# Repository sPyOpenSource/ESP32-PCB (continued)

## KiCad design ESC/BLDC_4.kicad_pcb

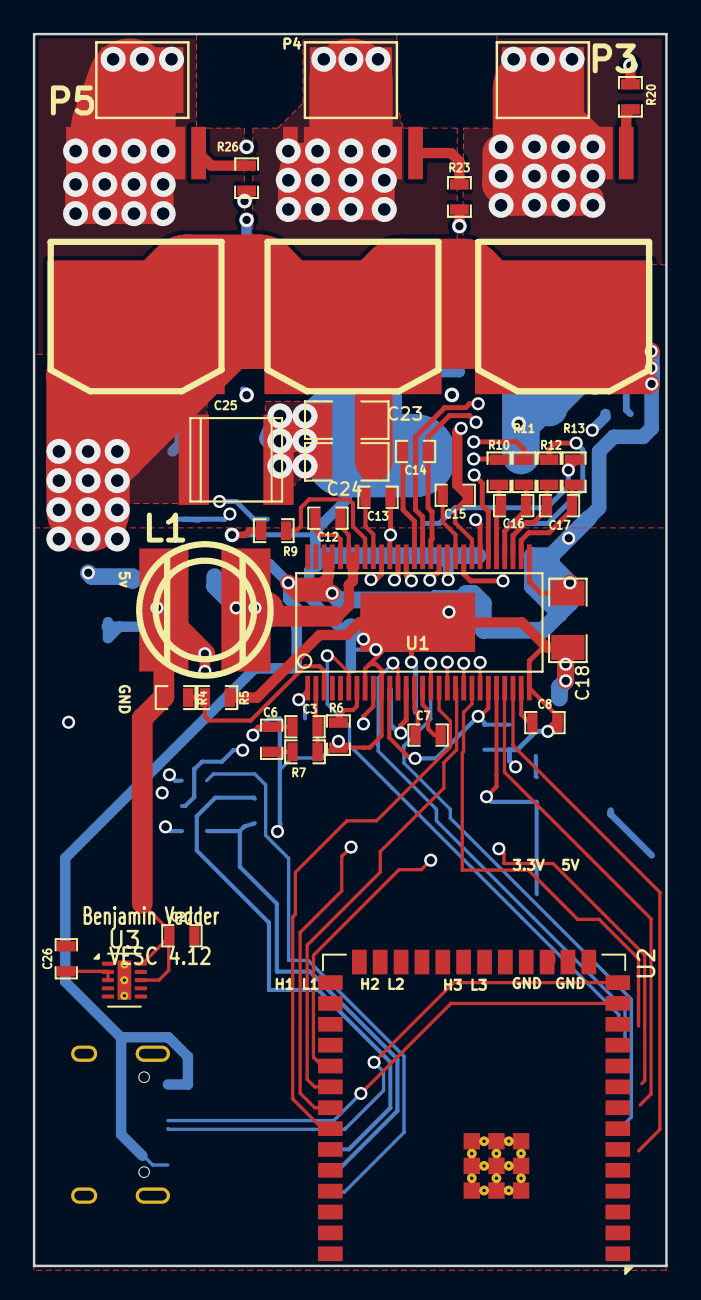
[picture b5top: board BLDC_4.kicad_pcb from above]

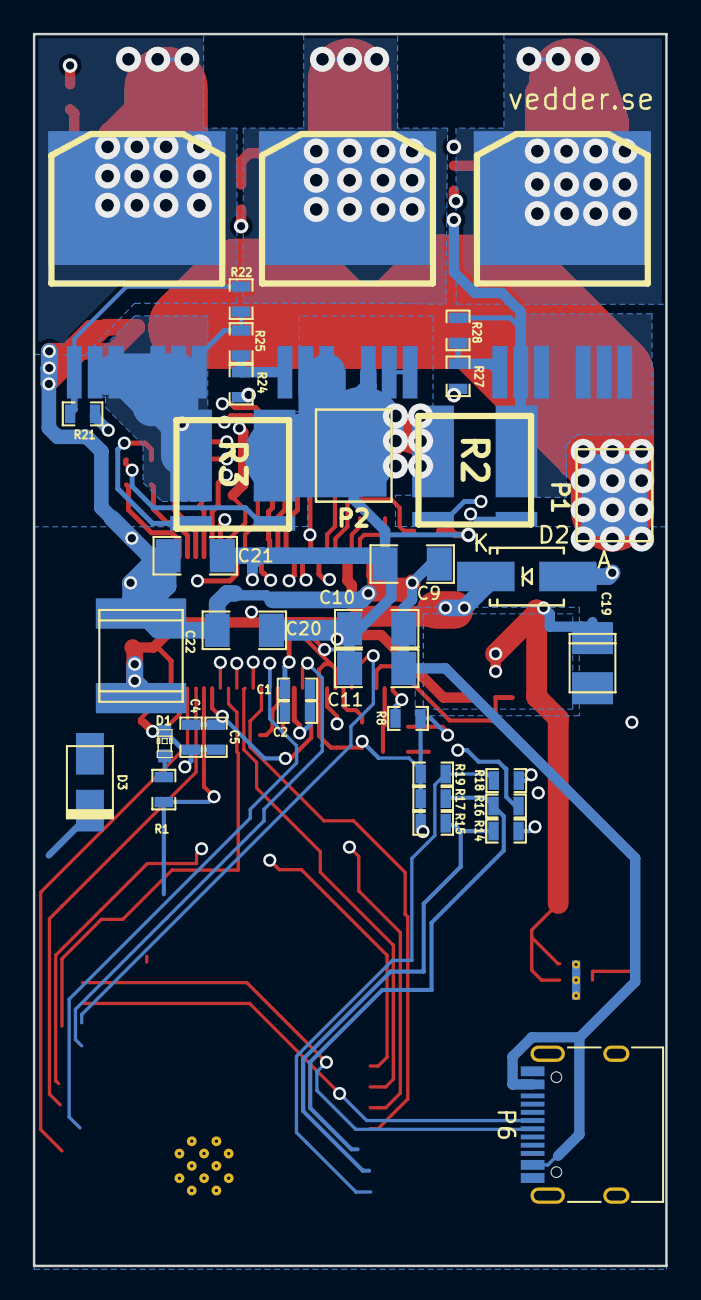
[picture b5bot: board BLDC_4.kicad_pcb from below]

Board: 4 copper layers, 38.5 x 75.0 mm, 74 parts (36 on the bottom side), 58 nets.

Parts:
C1, C2, C4, C5, C8: 2.2u; SMD-0603_c
C3: 120p; SMD-0603_c
C6: 6.8n; SMD-0603_c
C7: 22n; SMD-0603_c
C9, C10, C11, C18, C20, C21, C23, C24: 10u,50V; SMD-1206
C12: 100n; SMD-0603_c
C13, C14, C15: 220n; SMD-0603_c
C16, C17: 2.2n; SMD-0603_c
C19: 100u; c_tant_B
C22: 15u, 100v; c_2220
C25: 15u,100V; c_2220
C26, C27: C; SMD-0603_c
D1: LED; LED-0603
D2: DIODESCH; SMA_Handsoldering
D3: TVS 5V; do214ac
L1: 22u; inductor_smd_8x5mm
P1: IN+; 1PAD_4x5mm
P2: IN-; 1PAD_4x5mm
P3: MOTOR3; 1PAD_4x5mm
P4: MOTOR2; 1PAD_4x5mm
P5: MOTOR1; 1PAD_4x5mm
P6: USB_C_Plug_USB2.0; USB_C_Receptacle_HRO_TYPE-C-31-M-12
Q1, Q2, Q3, Q4, Q5, Q6: IRFS7530; D2PAK-7-GDS
R1, R15, R17, R19: 2k2; SMD-0603_r
R2, R3: SHUNT; WSLP2726
R4: 18k; SMD-0603_r
R5: 3k3; SMD-0603_r
R6: 10k; SMD-0603_r
R7: 15k; SMD-0603_r
R8: 220k; SMD-0603_r
R9: 1M; SMD-0603_r
R10, R11, R12, R13: 100R; SMD-0603_r
R14, R16, R18, R22, R25, R28: 39k; SMD-0603_r
R20, R21, R23, R24, R26, R27: 4R7; SMD-0603_r
U1: DRV8302; TSSOP-56-PP
U2: ESP32-S3-WROOM-2
U3: TPS62177DQC; WSON-10-1EP_2x3mm_P0.5mm_EP0.84x2.4mm_ThermalVias

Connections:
+5V: C19.1, C27.1, D3.2 (K), L1.2, R4.1, U3.8 (~SLEEP), U3.10 (VOS)
/Mosfet driver/H1_LOW: Q2.S, R3.2, R22.1, R25.1, U1.44 (SL_A)
/Mosfet driver/H1_VS: C13.1, P3.1, Q1.S, Q2.D, R18.1, U1.46 (SH_A)
/Mosfet driver/H2_VS: C14.1, P4.1, Q3.S, Q4.D, R16.1, U1.41 (SH_B)
/Mosfet driver/H3_LOW: Q6.S, R2.1, R28.1, U1.34 (SL_C)
/Mosfet driver/H3_VS: C15.1, P5.1, Q5.S, Q6.D, R14.1, U1.36 (SH_C)
/Mosfet driver/M_H1: R20.2, U1.47 (GH_A)
/Mosfet driver/M_H2: R23.2, U1.42 (GH_B)
/Mosfet driver/M_H3: R26.2, U1.37 (GH_C)
/Mosfet driver/M_L1: R21.2, U1.45 (GL_A)
/Mosfet driver/M_L2: R24.2, U1.40 (GL_B)
/Mosfet driver/M_L3: R27.2, U1.35 (GL_C)
/Mosfet driver/SH1_A: R2.3, R10.1
/Mosfet driver/SH1_B: R2.4, R11.1
/Mosfet driver/SH2_A: R3.4, R12.1
/Mosfet driver/SH2_B: R3.3, R13.1
EN: U1.16 (EN_GATE), U2.7 (IO7)
F: U1.6 (FAULT), U2.12 (IO8)
GND: C1.2, C2.2, C3.1, C4.1, C5.1, C6.1, C8.1, C9.2, C10.2, C11.2, C18.1, C19.2, C20.1, C21.1, C22.1, C23.1, C24.1, C25.1, C26.2, C27.2, D1.2 (K), D2.1 (A), D3.1 (A), P2.1, P6.A1 (GND), P6.A5 (CC), P6.A12 (GND), P6.B1 (GND), P6.B5 (VCONN), P6.B12 (GND), P6.S1 (SHIELD), Q4.S, R2.2, R3.1, R5.2, R6.2, R8.1, R9.1, R15.1, R17.1, R19.1, U1.8 (M_PWM), U1.10 (GAIN), U1.28 (AGND), U1.39 (SL_B), U1.57 (GND(POWER_PAD)), U3.1 (PGND), U3.5 (FB), U3.6 (AGND), U3.11 (PAD)
H1: U1.17 (INH_A), U2.34 (MTDI/IO41)
H2: U1.19 (INH_B), U2.32 (MTCK/IO39)
L1: U1.18 (INL_A), U2.33 (MTDO/IO40)
L2: U1.20 (INL_B), U2.31 (IO38)
unnamed: C6.2, R7.1
unnamed: D1.1 (A), R1.1
unnamed: C12.1, D2.2 (K), L1.1, U1.50 (PH), U1.51 (PH)
unnamed: P6.A6 (D+), U2.14 (USB_D+/IO20)
unnamed: P6.A7 (D-), U2.13 (USB_D-/IO19)
unnamed: Q1.G, R20.1
unnamed: Q2.G, R21.1, R22.2
unnamed: Q3.G, R23.1
unnamed: Q4.G, R24.1, R25.2
unnamed: Q5.G, R26.1
unnamed: Q6.G, R27.1, R28.2
unnamed: C8.2, U1.27 (AVDD)
unnamed: R9.2, U1.49 (BIAS)
unnamed: C13.2, U1.48 (BST_A)
unnamed: C14.2, U1.43 (BST_B)
unnamed: C12.2, U1.52 (BST_BK)
unnamed: C15.2, U1.38 (BST_C)
unnamed: C3.2, R7.2, U1.2 (COMP)
unnamed: C7.1, U1.14 (CP1)
unnamed: C7.2, U1.15 (CP2)
unnamed: R6.1, U1.7 (DTC)
unnamed: C4.2, C5.2, U1.11 (OC_ADJ), U1.23 (DVDD)
unnamed: C1.1, C2.1, U1.13 (GVDD)
unnamed: R8.2, U1.1 (RT_CLK)
unnamed: C16.1, R10.2, U1.33 (SN1)
unnamed: C17.1, R12.2, U1.31 (SN2)
unnamed: C16.2, R11.2, U1.32 (SP1)
unnamed: C17.2, R13.2, U1.30 (SP2)
unnamed: R4.2, R5.1, U1.3 (VSENSE)
unnamed: U2.1 (GND), U2.40 (GND), U2.41 (GND)
S1: R14.2, R15.2
S2: R16.2, R17.2
S3: R18.2, R19.2
VCC: R1.2, U1.9 (M_OC), U1.24 (REF)
V_SUPPLY: C9.1, C10.1, C11.1, C18.2, C20.2, C21.2, C22.2, C23.2, C24.2, C25.2, C26.1, P1.1, P6.A4 (VBUS), P6.A9 (VBUS), P6.B4 (VBUS), P6.B9 (VBUS), Q1.D, Q3.D, Q5.D, U1.29 (PVDD1), U1.53 (PVDD2), U1.54 (PVDD2), U3.2 (VIN), U3.3 (EN)

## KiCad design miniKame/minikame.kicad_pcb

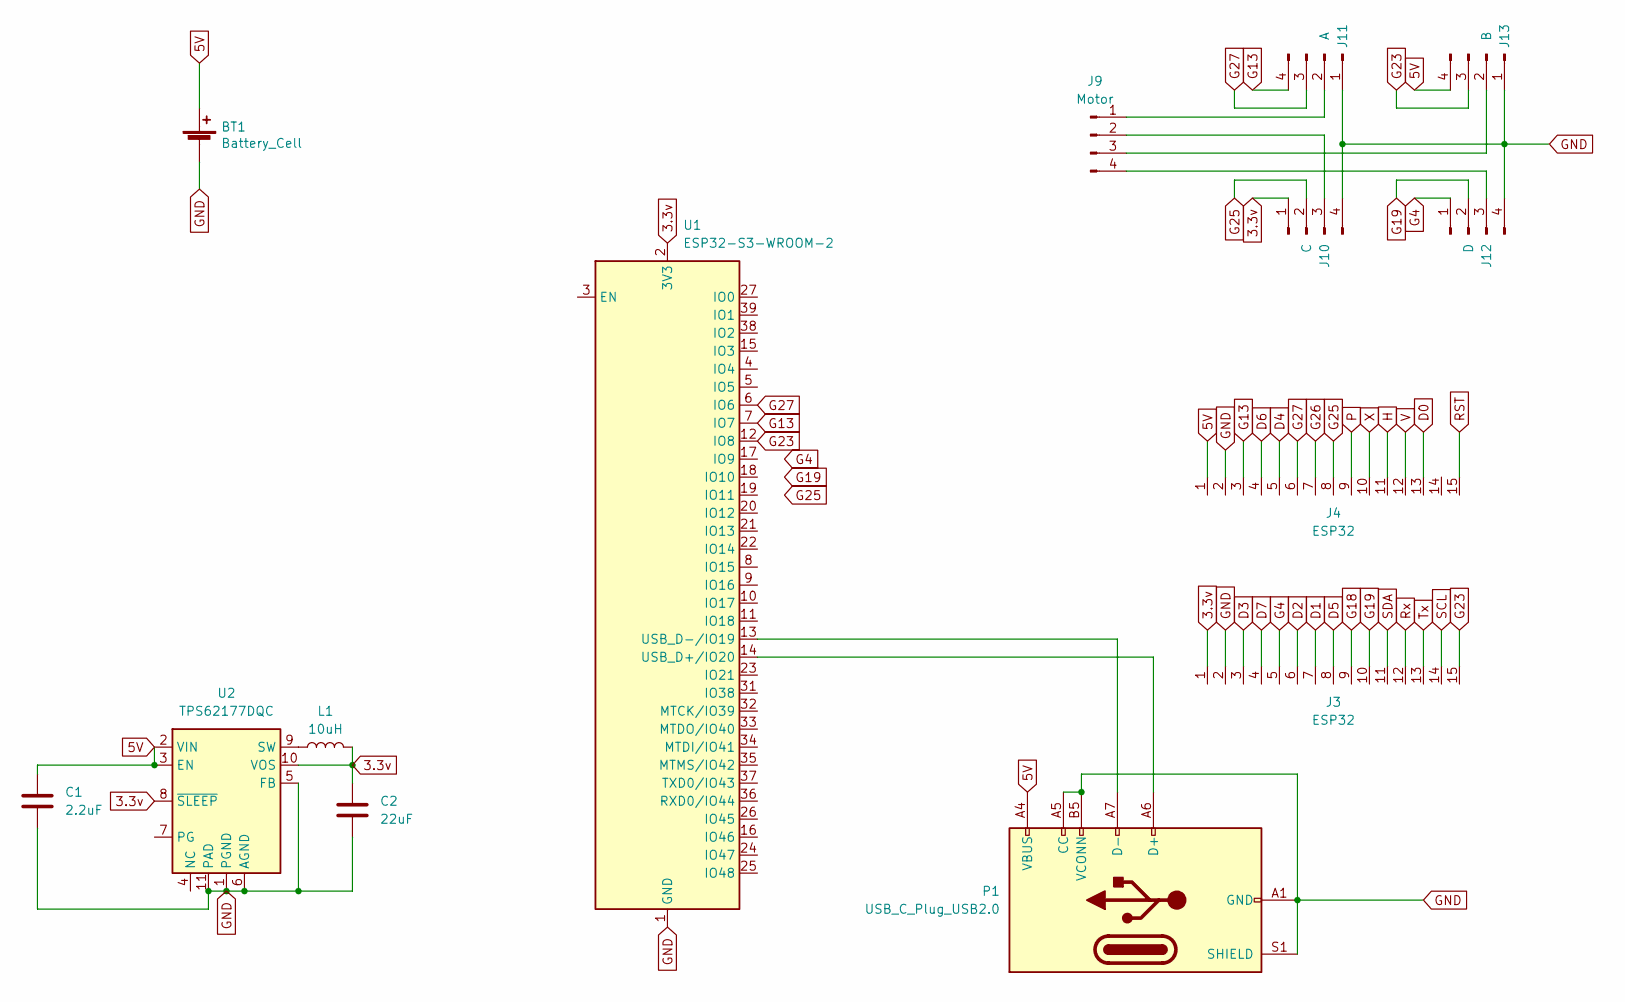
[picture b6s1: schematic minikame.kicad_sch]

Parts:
BT1: Battery_Cell; 1210
C1: 2.2uF; 0603
C2: 22uF; 0603
J3, J4: ESP32; PinHeader_1x15_P2.54mm_Vertical
J9: Motor
J10: C; 0603
J11: A
J12: D
J13: B
L1: 10uH
P1: USB_C_Plug_USB2.0; USB_C_Receptacle_HRO_TYPE-C-31-M-12
U1: ESP32-S3-WROOM-2
U2: TPS62177DQC; WSON-10-1EP_2x3mm_P0.5mm_EP0.84x2.4mm_ThermalVias

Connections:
3.3v: C2.1, J3.1, J10.1, L1.2, U1.2 (3V3), U2.8 (~SLEEP), U2.10 (VOS)
5V: BT1.1 (+), C1.1, J4.1, J13.4, P1.A4 (VBUS), P1.A9 (VBUS), P1.B4 (VBUS), P1.B9 (VBUS), U2.2 (VIN), U2.3 (EN)
D0: J4.13
D1: J3.7
D2: J3.6
D3: J3.3
D4: J4.5
D5: J3.8
D6: J4.4
D7: J3.4
G4: J3.5, J12.1
G13: J4.3, J11.4, U1.7 (IO7)
G18: J3.9
G19: J3.10, J12.2
G23: J3.15, J13.3, U1.12 (IO8)
G25: J4.8, J10.2
G26: J4.7
G27: J4.6, J11.3, U1.6 (IO6)
GND: BT1.2 (-), C1.2, C2.2, J3.2, J4.2, J10.4, J11.1, J12.4, J13.1, P1.A1 (GND), P1.A5 (CC), P1.A12 (GND), P1.B1 (GND), P1.B5 (VCONN), P1.B12 (GND), P1.S1 (SHIELD), U1.1 (GND), U1.40 (GND), U1.41 (GND), U2.1 (PGND), U2.5 (FB), U2.6 (AGND), U2.11 (PAD)
H: J4.11
unnamed: J9.2, J10.3
unnamed: J9.1, J11.2
unnamed: J9.4, J12.3
unnamed: J9.3, J13.2
unnamed: P1.A6 (D+), U1.14 (USB_D+/IO20)
unnamed: P1.A7 (D-), U1.13 (USB_D-/IO19)
unnamed: L1.1, U2.9 (SW)
P: J4.9
RST: J4.15
Rx: J3.12
SCL: J3.14
SDA: J3.11
Tx: J3.13
V: J4.12
X: J4.10

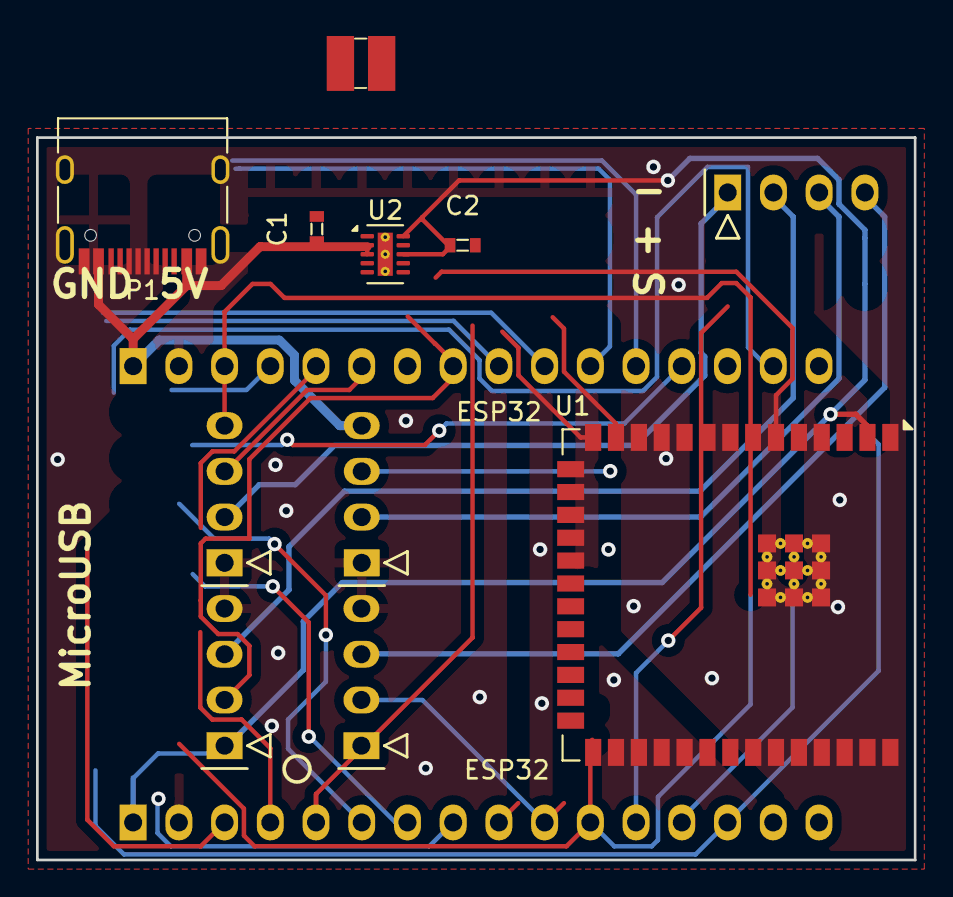
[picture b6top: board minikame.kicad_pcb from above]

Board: 2 copper layers, 48.8 x 40.1 mm, 13 parts (0 on the bottom side), 15 nets.

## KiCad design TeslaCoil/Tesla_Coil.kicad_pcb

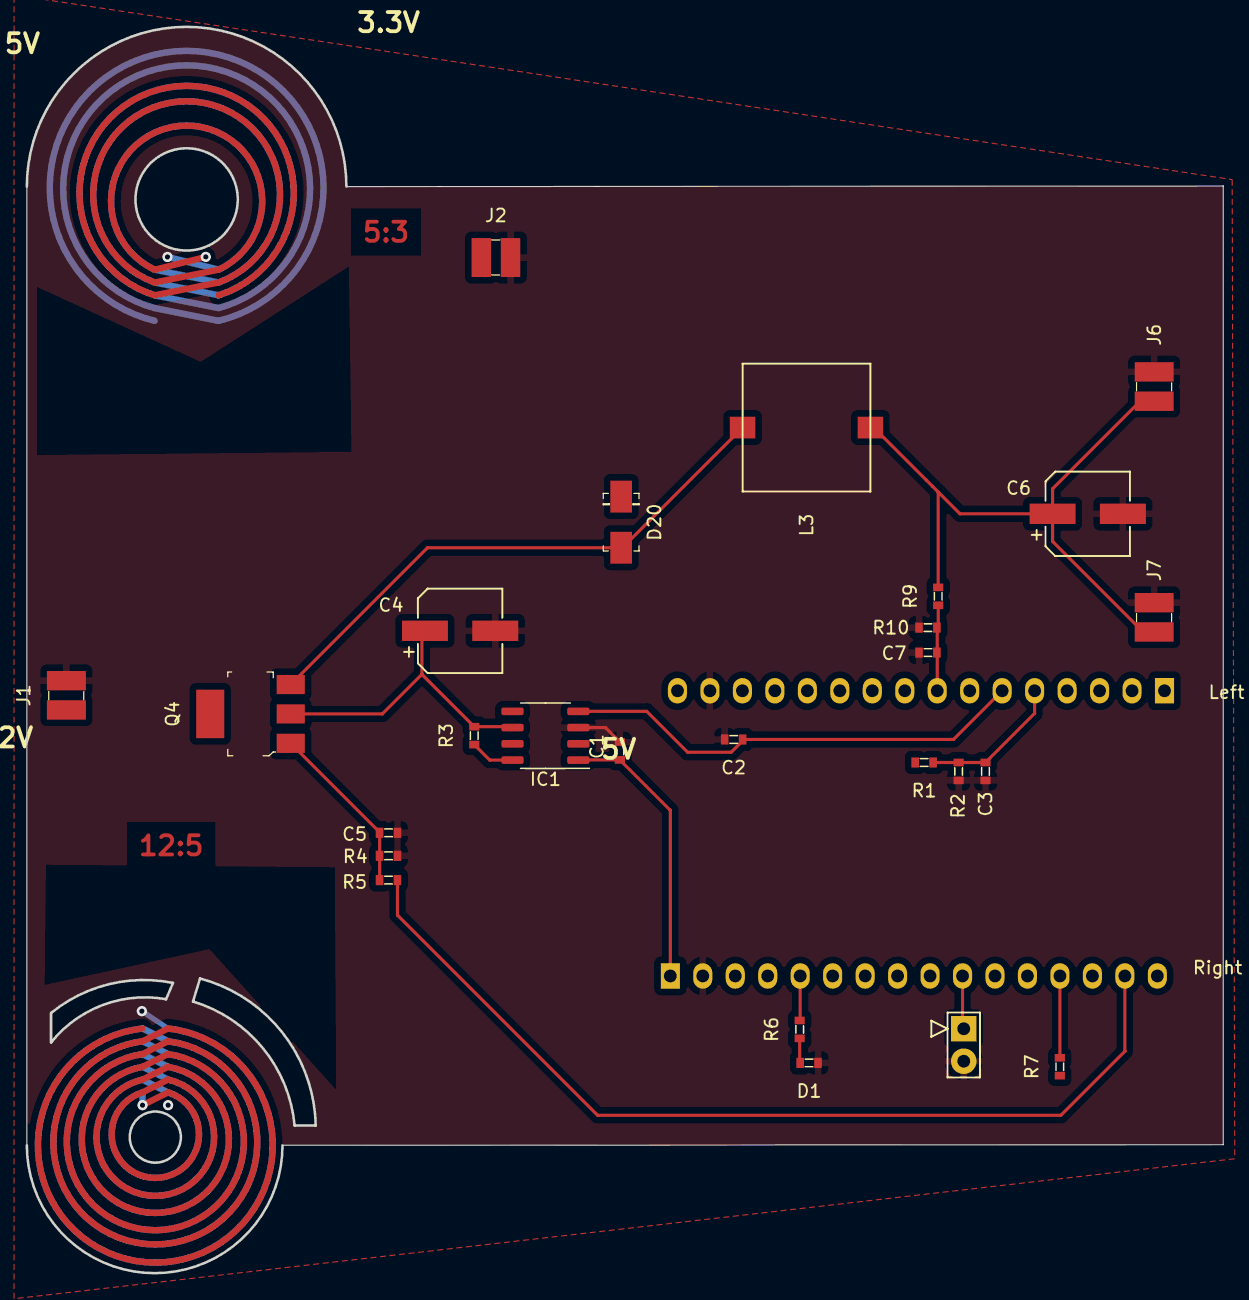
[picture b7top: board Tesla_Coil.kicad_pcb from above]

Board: 4 copper layers, 93.6 x 97.5 mm, 28 parts (0 on the bottom side), 15 nets.

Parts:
C1, C2, C3, C7: 0.1uF; 0603
C4: 100uF; Cpol-6.3x7.7
C5: 1nF; 0603
C6: 220uF; Cpol-6.3x7.7
D1: COMMS; 0603
D20: D_Schottky; DO-214AC
IC1: MAX4173H; SO-8_3.9x4.9mm_P1.27mm
J1: SOLAR_INPUT; 1210
J2: SOLAR_OUTPUT; 1210
J3: Left; PIN16
J4: Right; PIN16
J6: BATTERY_INPUT; 1210
J7: BATTERY_OUTPUT; 1210
L3: 33uH; 7447779139
Q4: IRFIZ44N; SOT-223
R1, R4, R9: 10k; 0603
R2, R6, R10: 560R; 0603
R3: 0.005R; 0603
R5: 100R; 0603
R7: 220R; 0603
RX1: GPIO; PIN2

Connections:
+3V3: C1.1, IC1.1 (VCC), J4.1
+12V: C4.1, IC1.6 (RS-), J2.1 (Sol+), Q4.2 (D), R3.2
Bat+: C6.1, J6.1, J7.1 (Bat+), L3.2, R9.2
GND: C1.2, C2.2, C3.2, C4.2, C5.1, C6.2, C7.2, D1.1 (K), IC1.3 (GND), J1.2 (Sol-), J2.2 (Sol-), J3.15, J4.2, J6.2, J7.2 (Bat-), R2.1, R4.2, R10.1, RX1.2
I_Sol: C2.1, IC1.4 (OUT), J3.6
unnamed: D1.2 (A), R6.1
unnamed: L3.1, Q4.3 (S)
unnamed: IC1.8 (RS+), J1.1 (Sol+), R1.2, R3.1
unnamed: J4.5, R6.2
unnamed: J4.10, RX1.1
unnamed: J4.13, R7.2
unnamed: C5.2, Q4.1 (G), R4.1, R5.1
PWM: J4.15, R5.2
U_Bat: C7.1, J3.8, R9.1, R10.2
U_Sol: C3.1, J3.5, R1.1, R2.2

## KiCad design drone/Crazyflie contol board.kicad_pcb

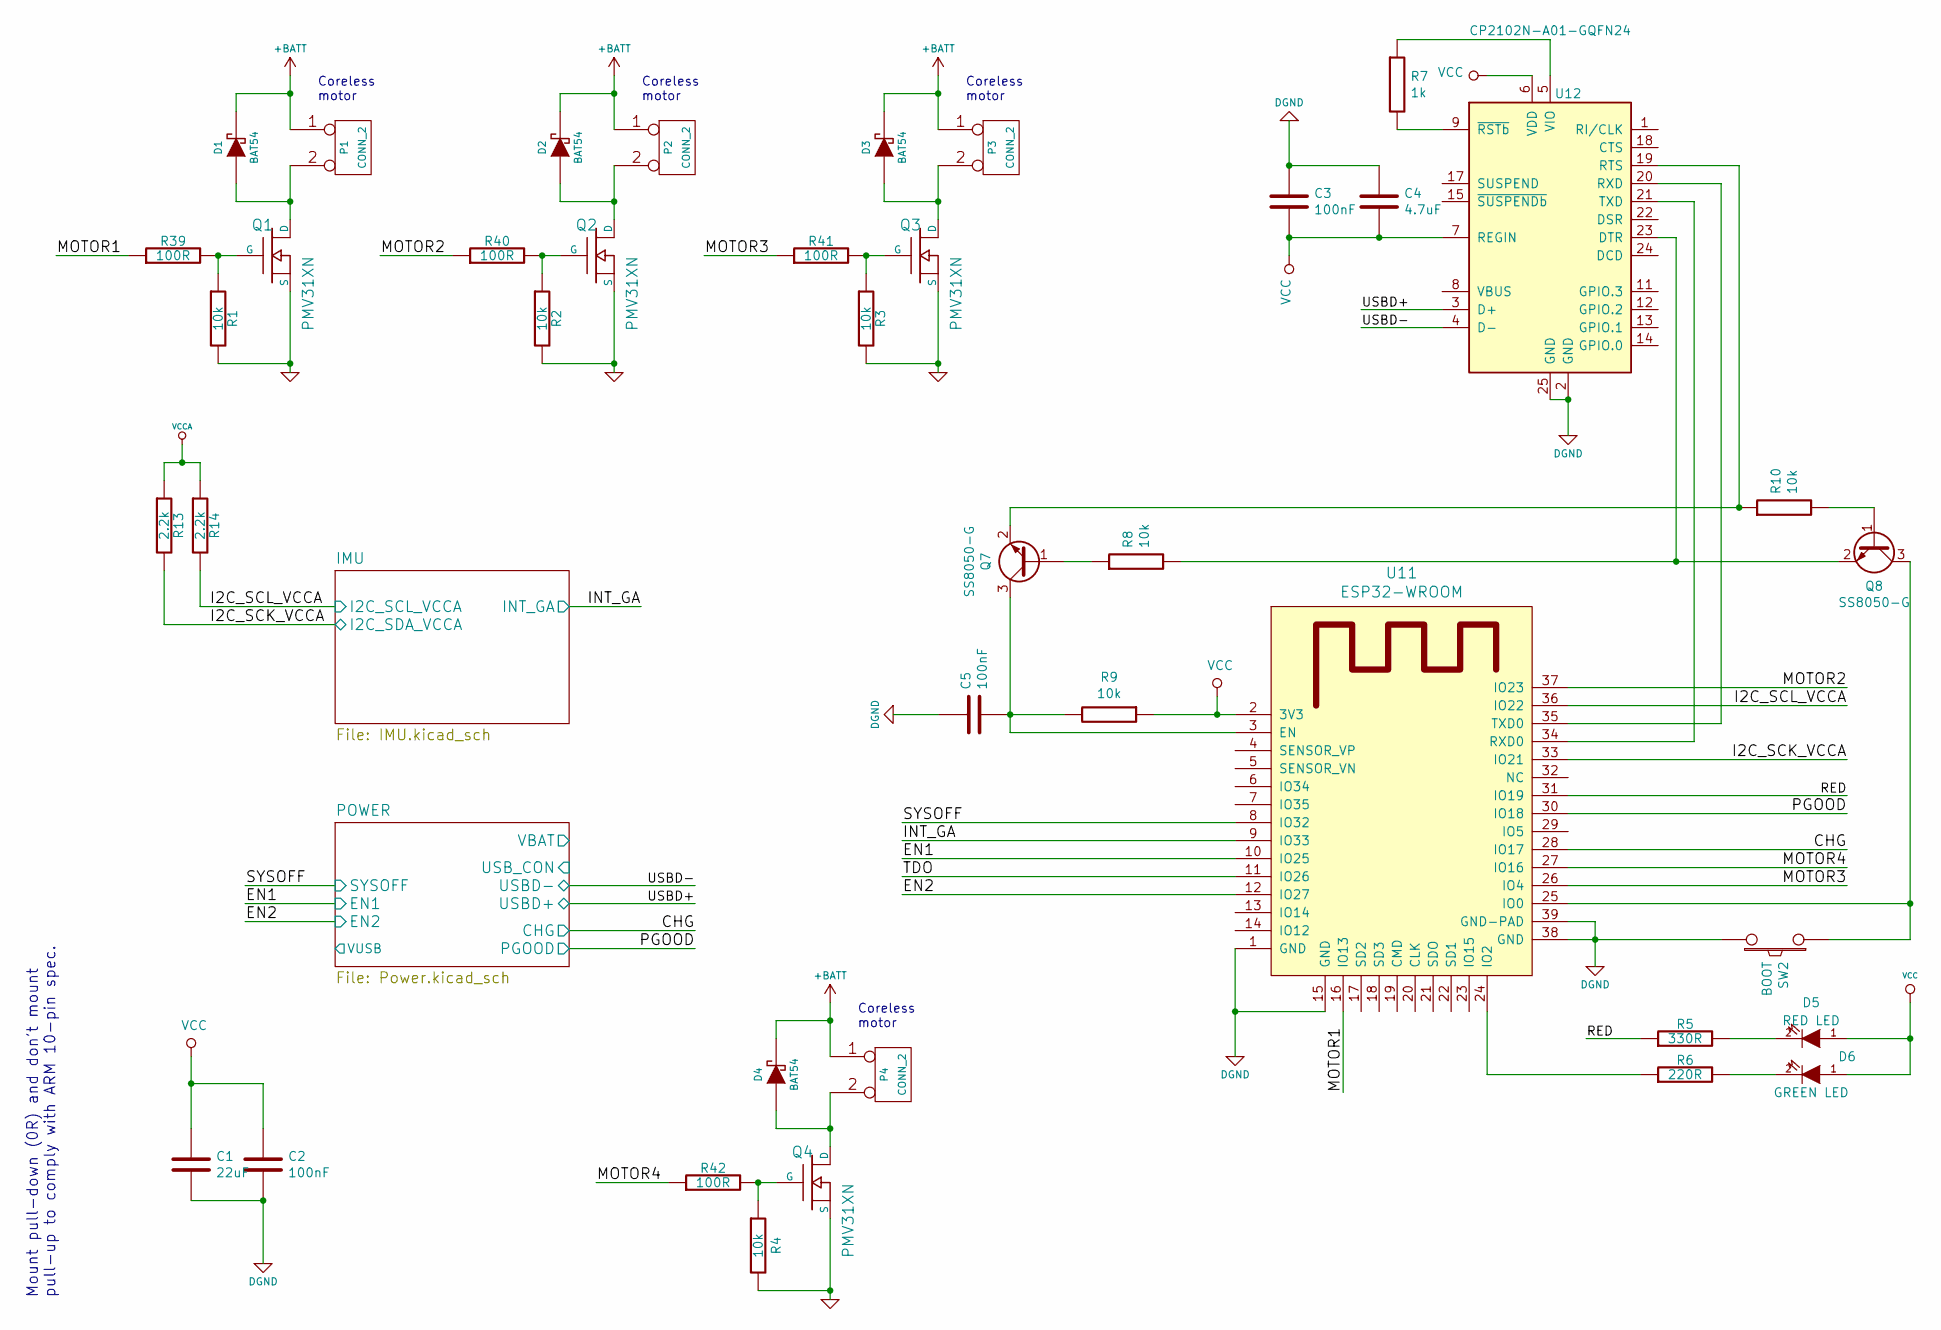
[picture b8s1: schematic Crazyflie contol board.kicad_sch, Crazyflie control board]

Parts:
C1: 22uF; 0603_new_new
C2, C3, C5: 100nF; 0603_new_new
C4: 4.7uF; 0603_new_new
D1, D2, D3, D4: BAT54; SOD323
D5: RED LED; SMDLED-0603
D6: GREEN LED; SMDLED-0603
P1, P2, P3, P4: CONN_2; PINHEADER_127_2X1
Q1, Q2, Q3, Q4: PMV31XN; SOT23GDS
Q7, Q8: SS8050-G; SOT-23-3
R1, R2, R3, R4: 10k; SM0402
R5: 330R; 0603_new_new
R6: 220R; 0603_new_new
R7: 1k; 0603_new_new
R8, R9, R10: 10k; 0603_new_new
R13, R14: 2.2k; 0603_new_new
R39, R40, R41: 100R; SM0402
R42: 100R; 0603
SW2: BOOT; Switch_Tactile_SMD_B3U-1000P_new_new
U11: ESP32-WROOM; ESP32-WROOM-32_new
U12: CP2102N-A01-GQFN24; QFN-24-1EP_4x4mm_new_new_new

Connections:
+BATT: D1.2 (K), D2.2 (K), D3.2 (K), D4.2 (K), P1.1, P2.1, P3.1, P4.1; also elsewhere on the board
/CHG: U11.28 (IO17); also elsewhere on the board
/EN1: U11.10 (IO25); also elsewhere on the board
/EN2: U11.12 (IO27); also elsewhere on the board
/I2C_SCK_VCCA: R13.2, U11.33 (IO21); also elsewhere on the board
/I2C_SCL_VCCA: R14.2, U11.36 (IO22); also elsewhere on the board
/INT_GA: U11.9 (IO33); also elsewhere on the board
/MOTOR1: R39.1, U11.16 (IO13)
/MOTOR2: R40.1, U11.37 (IO23)
/MOTOR3: R41.1, U11.26 (IO4)
/MOTOR4: R42.1, U11.27 (IO16)
/PGOOD: U11.30 (IO18); also elsewhere on the board
/RED: R5.1, U11.31 (IO19)
/SYSOFF: U11.8 (IO32); also elsewhere on the board
/USBD+: U12.3 (D+); also elsewhere on the board
/USBD-: U12.4 (D-); also elsewhere on the board
DGND: C1.2, C2.2, C3.1, C4.1, C5.1, SW2.2, U11.1 (GND), U11.15 (GND), U11.38 (GND), U11.39 (GND-PAD), U12.2 (GND), U12.25 (GND); also elsewhere on the board
GND: Q1.S, Q2.S, Q3.S, Q4.S, R1.2, R2.2, R3.2, R4.2; also elsewhere on the board
unnamed: C5.2, Q7.3 (C), R9.2, U11.3 (EN)
unnamed: D1.1 (A), P1.2 (PM), Q1.D
unnamed: D2.1 (A), P2.2 (PM), Q2.D
unnamed: D3.1 (A), P3.2 (PM), Q3.D
unnamed: D4.1 (A), P4.2 (PM), Q4.D
unnamed: D5.2 (K), R5.2
unnamed: D6.2 (K), R6.2
unnamed: Q1.G, R1.1, R39.2
unnamed: Q2.G, R2.1, R40.2
unnamed: Q3.G, R3.1, R41.2
unnamed: Q4.G, R4.1, R42.2
unnamed: Q7.1 (B), R8.1
unnamed: Q7.2 (E), R10.1, U12.19 (RTS)
unnamed: Q8.1 (B), R10.2
unnamed: Q8.2 (E), R8.2, U12.23 (DTR)
unnamed: Q8.3 (C), SW2.1, U11.25 (IO0)
unnamed: R6.1, U11.24 (IO2)
unnamed: R7.1, U12.5 (VIO)
unnamed: R7.2, U12.9 (~RSTb)
unnamed: U11.34 (RXD0), U12.21 (TXD)
unnamed: U11.35 (TXD0), U12.20 (RXD)
VCC: C1.1, C2.1, C3.2, C4.2, D5.1 (A), D6.1 (A), R9.1, U11.2 (3V3), U12.6 (VDD), U12.7 (REGIN); also elsewhere on the board
VCCA: R13.1, R14.1; also elsewhere on the board

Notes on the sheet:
Coreless motor
Mount pull-down (0R) and don't mount pull-up to comply with ARM 10-pin spec.

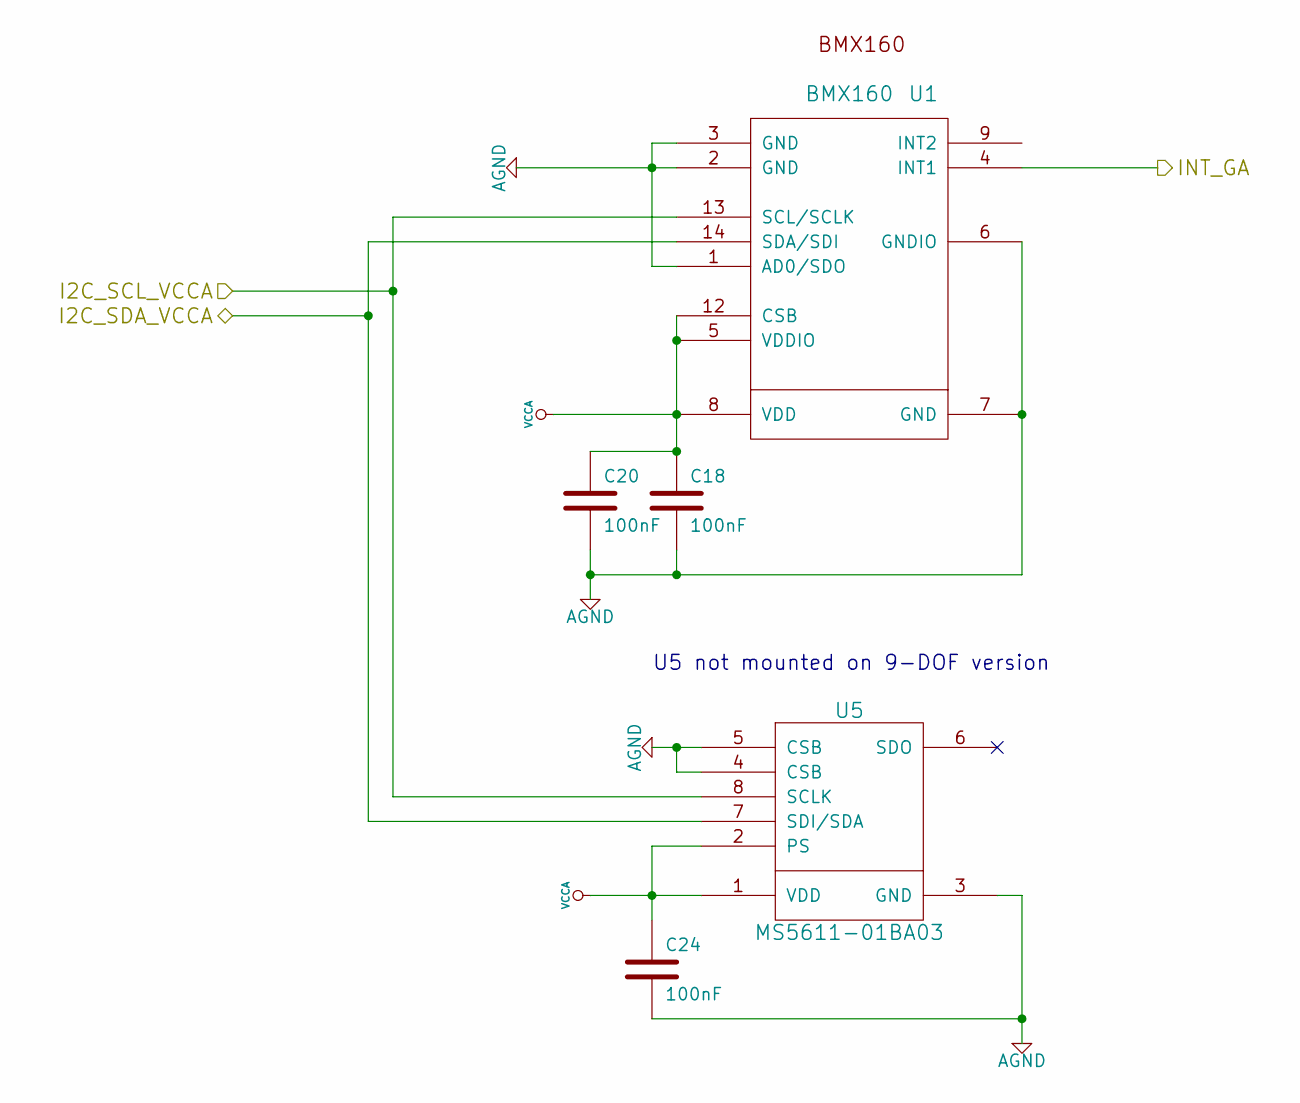
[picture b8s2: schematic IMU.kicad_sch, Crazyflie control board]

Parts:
C18, C20, C24: 100nF; 0603_new_new
U1: BMX160; LGA-14L_2.5x3mm__LSM6DS3
U5: MS5611-01BA03; MS5611

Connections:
/I2C_SCK_VCCA: U1.14 (SDA/SDI), U5.7 (SDI/SDA); also elsewhere on the board
/I2C_SCL_VCCA: U1.13 (SCL/SCLK), U5.8 (SCLK); also elsewhere on the board
/INT_GA: U1.4 (INT1); also elsewhere on the board
AGND: C18.2, C20.2, C24.2, U1.1 (AD0/SDO), U1.2 (GND), U1.3 (GND), U1.6 (GNDIO), U1.7 (GND), U5.3 (GND), U5.4 (CSB), U5.5 (CSB); also elsewhere on the board
VCCA: C18.1, C20.1, C24.1, U1.5 (VDDIO), U1.8 (VDD), U1.12 (CSB), U5.1 (VDD), U5.2 (PS); also elsewhere on the board

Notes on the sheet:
U5 not mounted on 9-DOF version

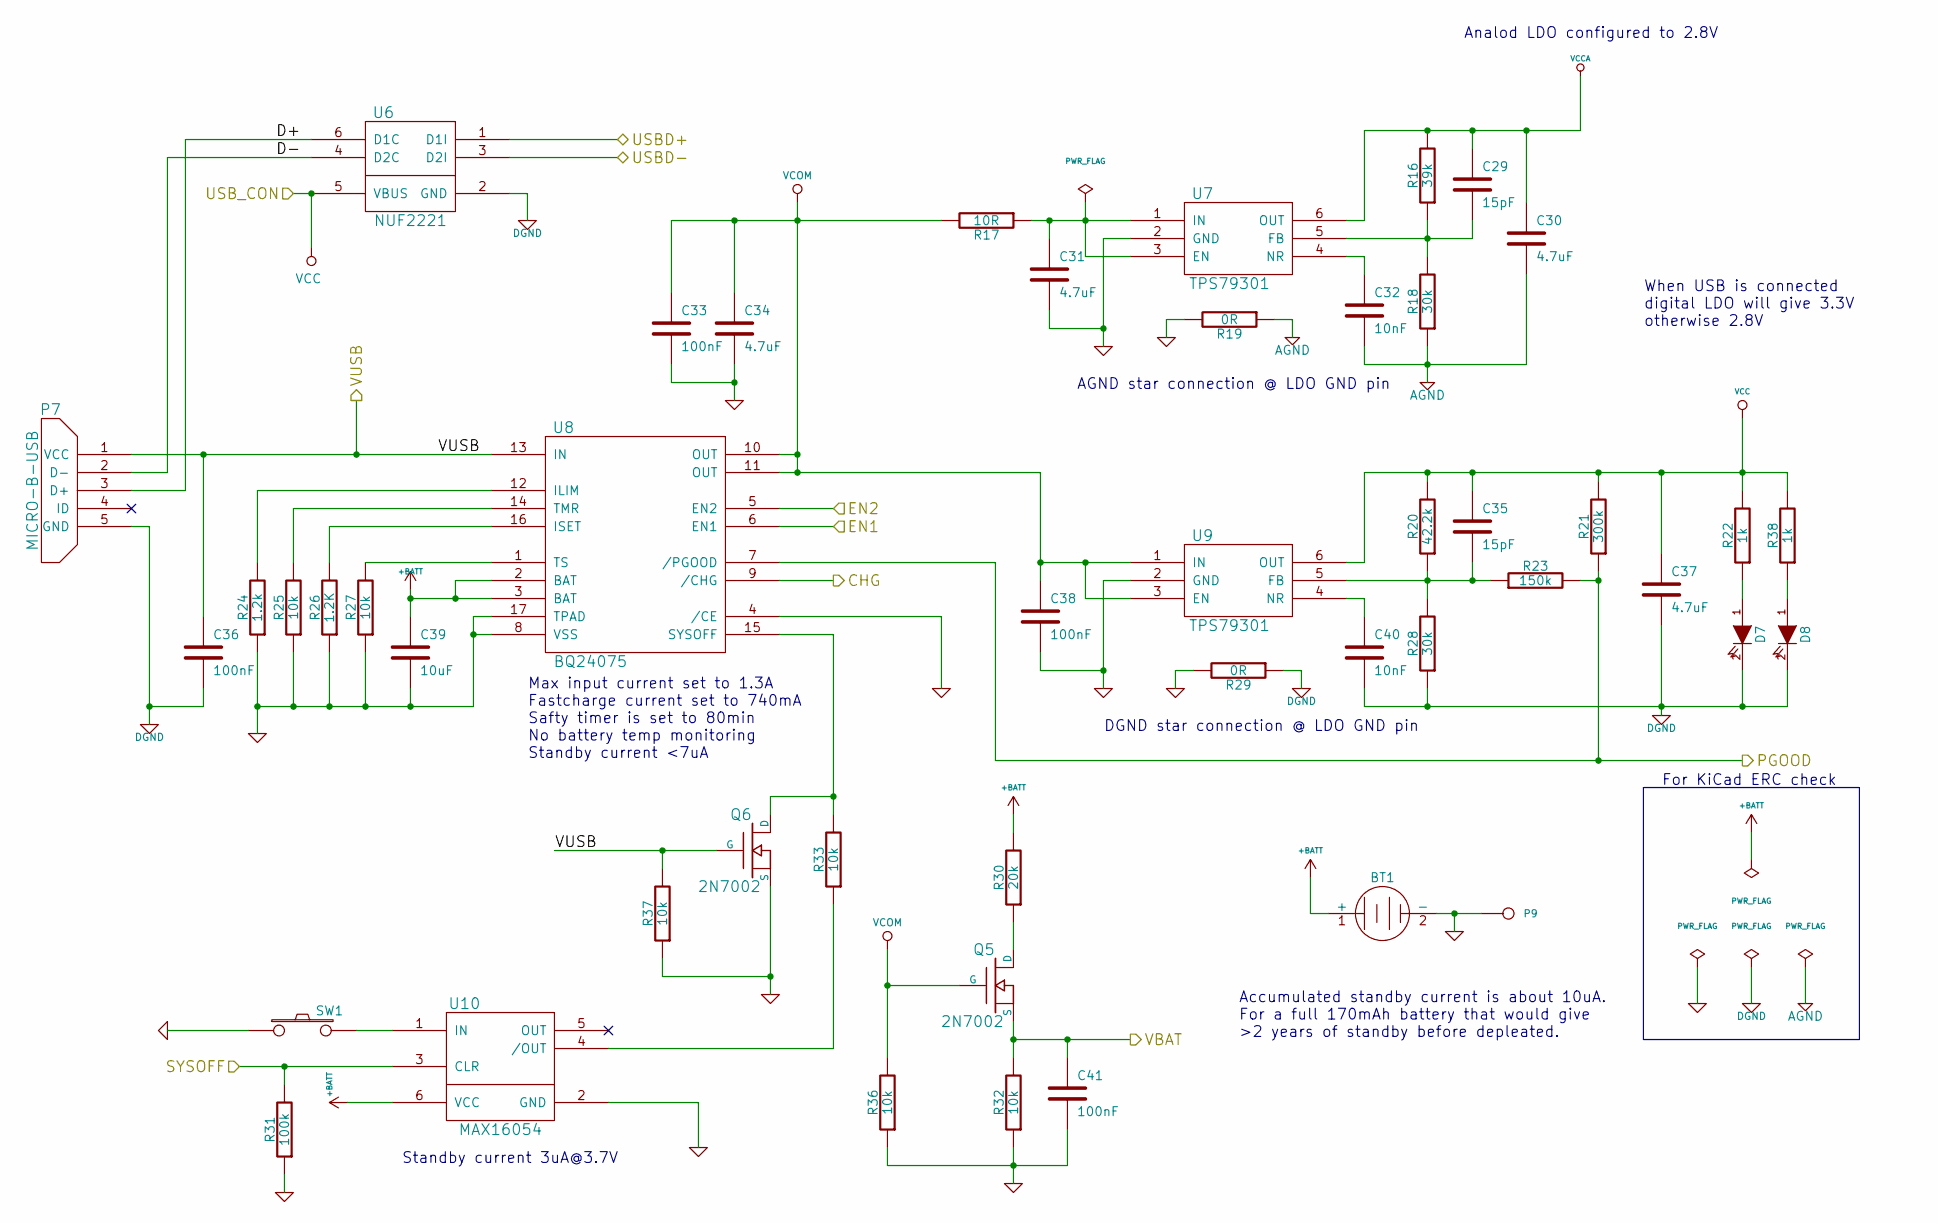
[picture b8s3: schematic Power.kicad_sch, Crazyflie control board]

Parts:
BT1: BATTERY; JST-B2B-ZR
C29, C35: 15pF; 0603_new_new
C30, C31, C34, C37: 4.7uF; 0603_new_new
C32, C40: 10nF; 0603_new_new
C33, C36, C38, C41: 100nF; 0603_new_new
C39: 10uF; 0603_new_new
D7, D8: BLUE LED; SMDLED-0603
P7: MICRO-B-USB; ZX62-B-5PA_11_CFK
P9: CONN_1; PINHEADER_127_1X1
Q5, Q6: 2N7002; SOT23GDS
R16: 39k; 0603_new_new
R17: 10R; 0603_new_new
R18, R28: 30k; 0603_new_new
R19, R29: 0R; 0603_new_new
R20: 42.2k; 0603_new_new
R21: 300k; 0603_new_new
R22, R38: 1k; 0603_new_new
R23: 150k; 0603_new_new
R24: 1.2k; 0603_new_new
R25, R27, R32, R33, R36, R37: 10k; 0603_new_new
R26: 1.2K; 0603_new_new
R30: 20k; 0603_new_new
R31: 100k; 0603_new_new
SW1: PUSH ON/OFF; SPST-NO-4x2.5
U6: NUF2221; SOT363
U7, U9: TPS79301; SOT23_6
U8: BQ24075; QFN16
U10: MAX16054; SOT23_6

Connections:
+BATT: BT1.1 (+), C39.1, R30.2, U8.2 (BAT), U8.3 (BAT), U10.6 (VCC); also elsewhere on the board
/CHG: U8.9 (/CHG); also elsewhere on the board
/EN1: U8.6 (EN1); also elsewhere on the board
/EN2: U8.5 (EN2); also elsewhere on the board
/PGOOD: R21.1, R23.2, U8.7 (/PGOOD); also elsewhere on the board
/POWER/D+: P7.3 (D+), U6.6 (D1C)
/POWER/D-: P7.2 (D-), U6.4 (D2C)
/POWER/VBAT: C41.1, Q5.S, R32.2
/POWER/VUSB: C36.1, P7.1 (VCC), Q6.G, R37.2, U8.13 (IN)
/SYSOFF: R31.2, U10.3 (CLR); also elsewhere on the board
/USBD+: U6.1 (D1I); also elsewhere on the board
/USBD-: U6.3 (D2I); also elsewhere on the board
AGND: C30.2, C32.2, R18.1, R19.1; also elsewhere on the board
DGND: C36.2, C37.2, C40.2, D7.2 (K), D8.2 (K), P7.5 (GND), R28.1, R29.1, U6.2 (GND); also elsewhere on the board
GND: BT1.2 (-), C31.2, C33.2, C34.2, C38.2, C39.2, C41.2, P9.1, Q6.S, R19.2, R24.1, R25.1, R26.1, R27.1, R29.2, R31.1, R32.1, R36.1, R37.1, SW1.1, U7.2 (GND), U8.4 (/CE), U8.8 (VSS), U8.17 (TPAD), U9.2 (GND), U10.2 (GND); also elsewhere on the board
unnamed: C29.2, R16.1, R18.2, U7.5 (FB)
unnamed: C31.1, R17.1, U7.1 (IN), U7.3 (EN)
unnamed: C32.1, U7.4 (NR)
unnamed: C35.2, R20.1, R23.1, R28.2, U9.5 (FB)
unnamed: C40.1, U9.4 (NR)
unnamed: D7.1 (A), R22.1
unnamed: D8.1 (A), R38.1
unnamed: Q5.D, R30.1
unnamed: Q6.D, R33.2, U8.15 (SYSOFF)
unnamed: R24.2, U8.12 (ILIM)
unnamed: R25.2, U8.14 (TMR)
unnamed: R26.2, U8.16 (ISET)
unnamed: R27.2, U8.1 (TS)
unnamed: R33.1, U10.4 (/OUT)
unnamed: SW1.2, U10.1 (IN)
VCC: C35.1, C37.1, R20.2, R21.2, R22.2, R38.2, U6.5 (VBUS), U9.6 (OUT); also elsewhere on the board
VCCA: C29.1, C30.1, R16.2, U7.6 (OUT); also elsewhere on the board
VCOM: C33.1, C34.1, C38.1, Q5.G, R17.2, R36.2, U8.10 (OUT), U8.11 (OUT), U9.1 (IN), U9.3 (EN)

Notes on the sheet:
DGND star connection @ LDO GND pin
Accumulated standby current is about 10uA. For a full 170mAh battery that would give >2 years of standby before depleated.
Max input current set to 1.3A Fastcharge current set to 740mA Safty timer is set to 80min No battery temp monitoring Standby current <7uA
Analod LDO configured to 2.8V
AGND star connection @ LDO GND pin
Standby current 3uA@3.7V
When USB is connected digital LDO will give 3.3V otherwise 2.8V
For KiCad ERC check

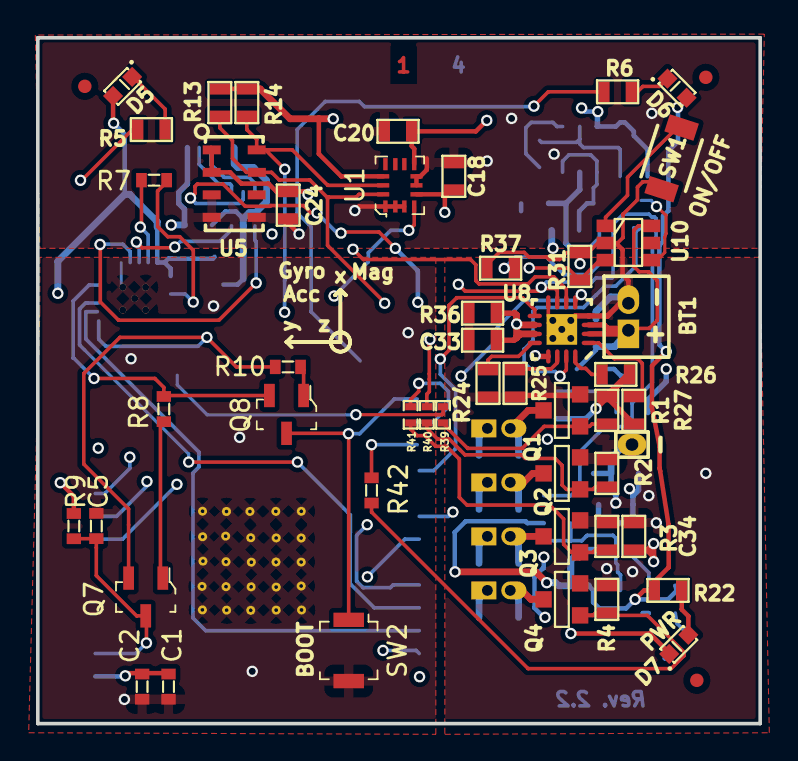
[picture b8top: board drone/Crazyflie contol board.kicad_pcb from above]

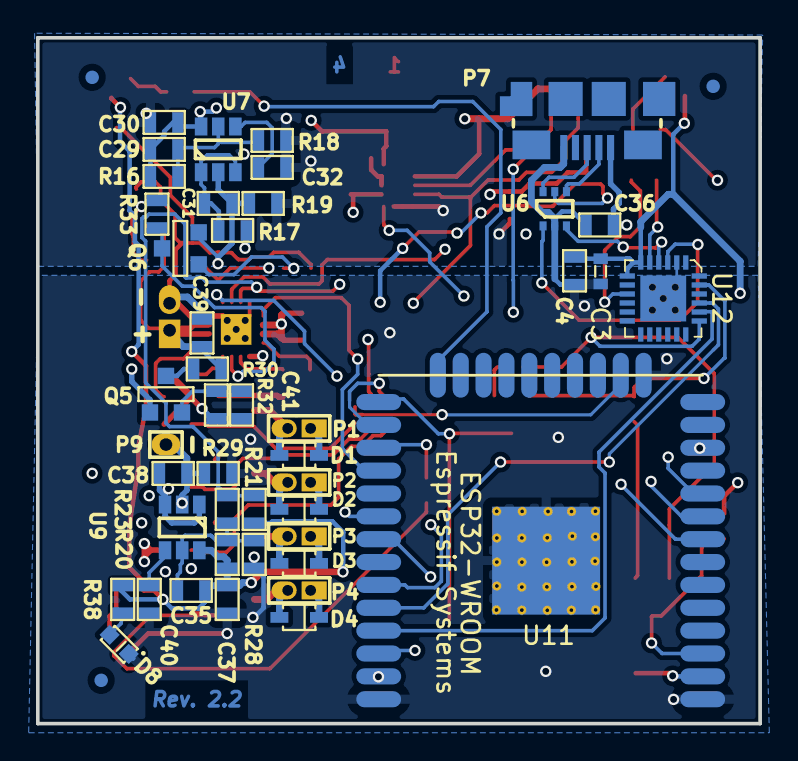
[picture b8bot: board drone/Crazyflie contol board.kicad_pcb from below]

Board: 4 copper layers, 40.1 x 38.1 mm, 92 parts (44 on the bottom side), 62 nets.

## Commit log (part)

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2019-02-24 initial version
2019-02-27 new version
2019-02-27 better version
2019-03-01 working version
2019-03-09 improved version
2019-03-10 final versrion
2020-05-06 version 2.0
2020-05-12 checked: esp32 pins (issue #2)
2021-06-13 jlpcb fix
2022-07-04 ESP32
2022-07-04 merge
2022-07-04 updated: miniKame
2022-07-04 rename
2022-08-04 save
2022-08-05 added: ESC
2022-08-07 finished
2022-08-07 drone: filling
